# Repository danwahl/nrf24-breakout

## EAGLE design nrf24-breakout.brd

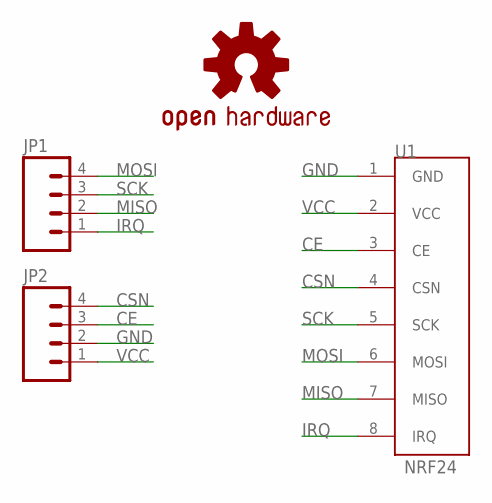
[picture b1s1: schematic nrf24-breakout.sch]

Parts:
JP1, JP2: M04NO_SILK_ALL_ROUND; 1X04_NO_SILK_ALL_ROUND
LOGO1: OSHW-LOGOS; OSHW-LOGO-S
U1: NRF24

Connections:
CE: JP2.3, U1.3 (CE)
CSN: JP2.4, U1.4 (CSN)
GND: JP2.2, U1.1 (GND)
IRQ: JP1.1, U1.8 (IRQ)
MISO: JP1.2, U1.7 (MISO)
MOSI: JP1.4, U1.6 (MOSI)
SCK: JP1.3, U1.5 (SCK)
VCC: JP2.1, U1.2 (VCC)

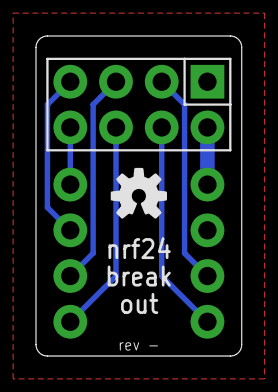
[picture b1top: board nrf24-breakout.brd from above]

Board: 2 copper layers, 11.4 x 17.8 mm, 4 parts (0 on the bottom side), 8 nets.

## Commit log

2015-11-29 added ground plane, widened vcc trace
2015-11-29 small aesthetic changes

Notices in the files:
parts and their libraries:
SparkFun-Connectors: Licensing: Creative Commons ShareAlike 4.0 International - https://creativecommons.org/licenses/by-sa/4.0
